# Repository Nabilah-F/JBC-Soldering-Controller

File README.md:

# JBC-Soldering-Controller

The idea of this project is to make a JBC soldering station for the T245, T210, HT420 and PA120 Micro Tweezers. 
It runs from a 12V to 24V DC power supply.

Tested:

T245 soldering iron

Todo:

Automatically changing the GUI depending on if you are using the standard iron or the tweezers.
Update FW to use tweezers.

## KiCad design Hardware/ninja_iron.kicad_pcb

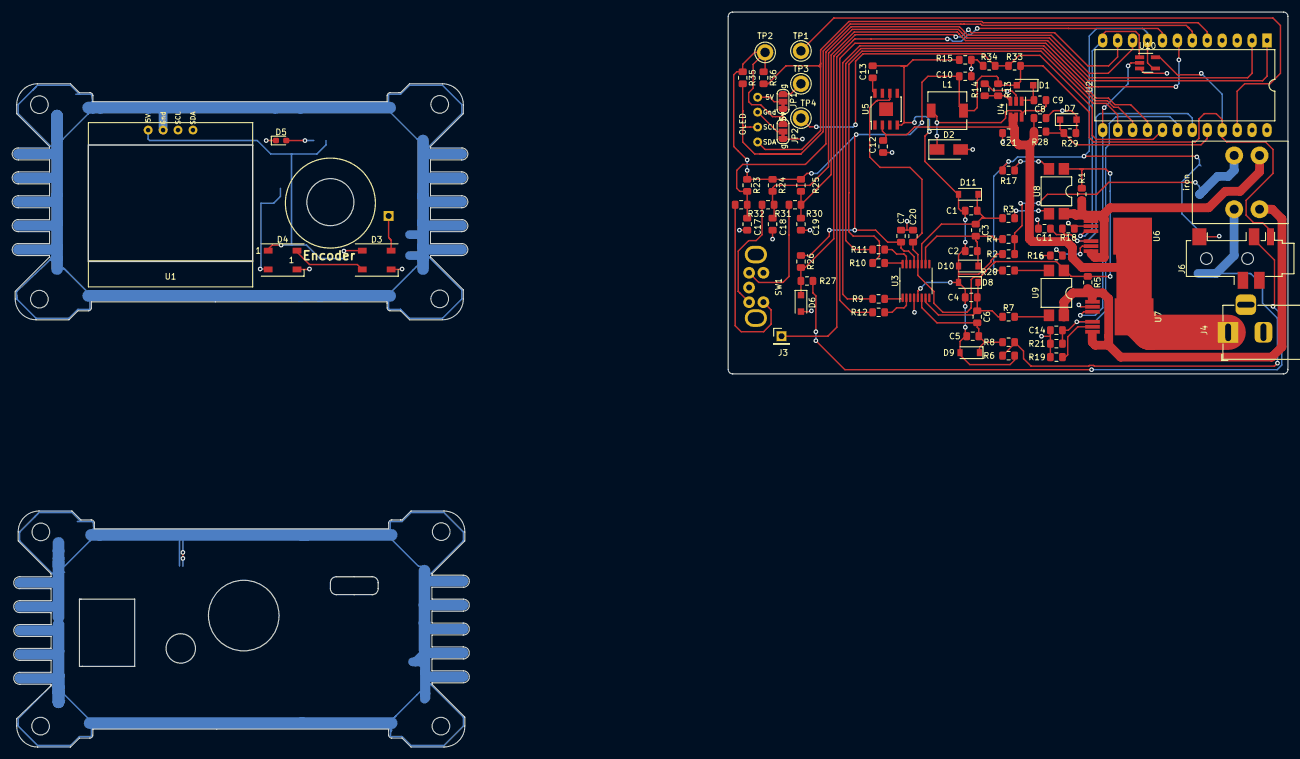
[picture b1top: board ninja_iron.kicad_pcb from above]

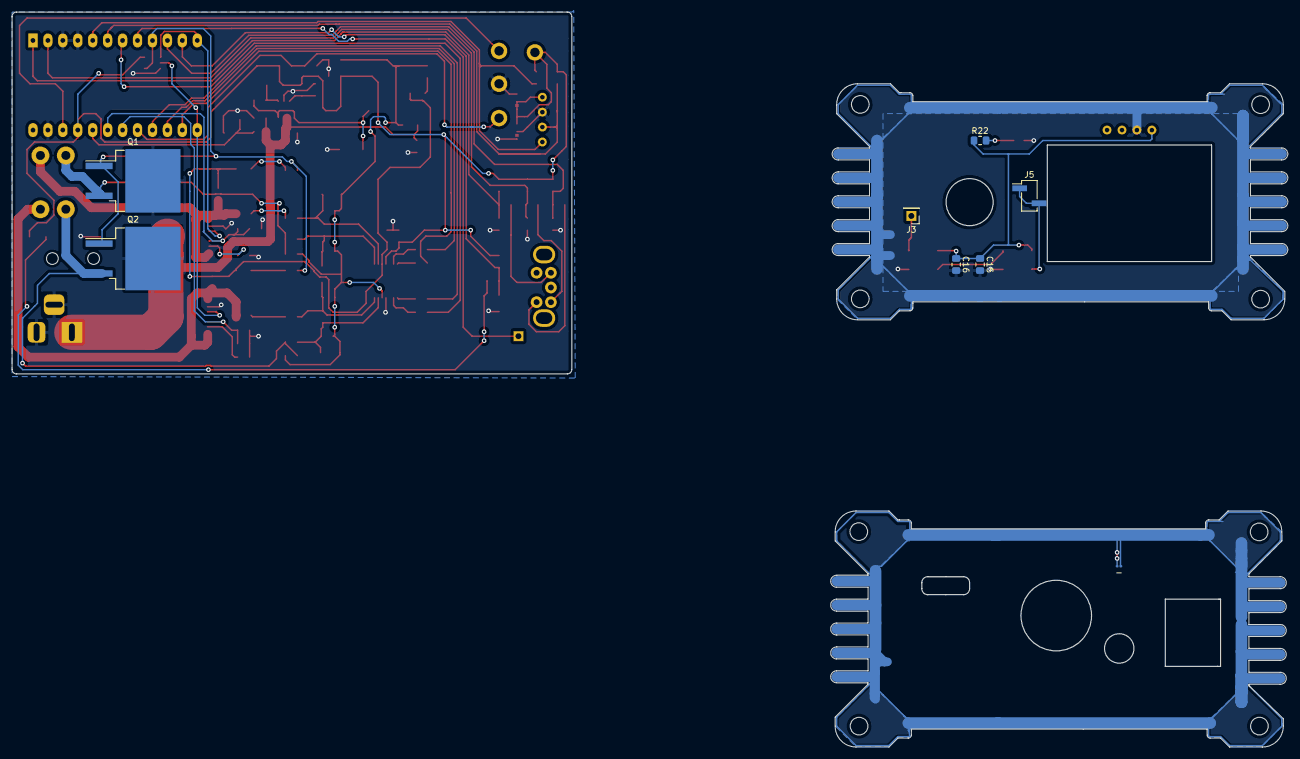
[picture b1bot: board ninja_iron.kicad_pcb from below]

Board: 2 copper layers, 216.8 x 124.9 mm, 96 parts (8 on the bottom side), 52 nets.

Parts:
-: R_0201_0603Metric
C1, C2, C4, C5: 0.047uF; C_0805_2012Metric_Pad1.15x1.40mm_HandSolder
C3, C6: 0.47uF; C_0805_2012Metric_Pad1.15x1.40mm_HandSolder
C7, C9, C12, C13, C15, C16, C20: 0.1uF; C_0805_2012Metric_Pad1.15x1.40mm_HandSolder
C8: 10uF; C_0805_2012Metric_Pad1.15x1.40mm_HandSolder
C10: 20uF; C_0805_2012Metric_Pad1.15x1.40mm_HandSolder
C11, C14, C17, C18, C19: 10nF; C_0805_2012Metric_Pad1.15x1.40mm_HandSolder
C21: 1uF; C_0805_2012Metric_Pad1.15x1.40mm_HandSolder
D1: 1N4448; D_SOD-123F
D2: B140-E3; D_SMA
D3, D4: WS2812B; LED_WS2812B_PLCC4_5.0x5.0mm_P3.2mm
D5: LED; LED_0603_1608Metric_Pad1.05x0.95mm_HandSolder
D6, D7: D; D_SOD-123F
D8, D9, D10, D11: 4V7; D_SOD-123
J3, J3#2: Conn_01x01; PinHeader_1x01_P2.54mm_Vertical
J4: Barrel_Jack_Switch; BarrelJack_Horizontal
J5: Conn_01x01; PinHeader_1x02_P2.54mm_Vertical_SMD_Pin1Left
J6: Audio-Jack-3; Jack_3.5mm_Horizontal
JP1, JP2: -; SolderJumper-3_P1.3mm_Bridged12_RoundedPad1.0x1.5mm_NumberL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
L1: 22uH; L_6.3x6.3_H3
OLED: pin_oled
Q1, Q2: Q_NMOS_GSD; TO-263-2
R1, R2, R5, R6: 100k; R_0805_2012Metric_Pad1.15x1.40mm_HandSolder
R3, R4, R7, R8: 820; R_0805_2012Metric_Pad1.15x1.40mm_HandSolder
R9, R10, R11, R12: 51; R_0805_2012Metric_Pad1.15x1.40mm_HandSolder
R13: 52.3k; R_0805_2012Metric_Pad1.15x1.40mm_HandSolder
R14, R16, R19, R23, R24, R25, R26, R35, R36: 10k; R_0805_2012Metric_Pad1.15x1.40mm_HandSolder
R15: 0R; R_0805_2012Metric_Pad1.15x1.40mm_HandSolder
R17, R20: 750R; R_0805_2012Metric_Pad1.15x1.40mm_HandSolder
R18, R21: 1k2; R_0805_2012Metric_Pad1.15x1.40mm_HandSolder
R22: 330; R_0805_2012Metric_Pad1.15x1.40mm_HandSolder
R27, R30, R31, R32: 100; R_0805_2012Metric_Pad1.15x1.40mm_HandSolder
R28: 30k; R_0805_2012Metric_Pad1.15x1.40mm_HandSolder
R29: 5k1; R_0805_2012Metric_Pad1.15x1.40mm_HandSolder
R33, R34: DNF; R_0805_2012Metric_Pad1.15x1.40mm_HandSolder
SW1: Rotary_Encoder_Switch; rot_encoder_alt
TP1, TP2, TP3, TP4: TestPoint; TestPoint_Keystone_5005-5009_Compact
U1: OLED_I2C_128x32; OLED_I2C_128x32_alt
U2: arduino_pro_micro; DIP-24_W15.24mm_LongPads
U3: ADS1120-PW; TSSOP-16_4.4x5mm_P0.65mm
U4: MCP16301; SOT-23-6_Handsoldering
U5: AD586; SOIC-8-1EP_3.9x4.9mm_P1.27mm_EP2.35x2.35mm
U6, U7: VN5E010; HPAK
U8, U9: FODM3011; SMDIP-4_W7.62mm
U10: 74LVC1G32; SOT-23-5_HandSoldering
iron: neutrik_modified

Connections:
+5VA: C20.1, R1.2, R5.1, U3.12, U5.6, U8.1, U9.1
+5VD: C7.1, C10.1, C15.1, C16.1, D1.2, D3.1, D4.1, J6.1, JP1.1, JP1.2, JP2.3, L1.2, OLED.1, R13.1, R22.1, R23.1, R24.1, R25.1, R26.1, R33.1, R35.1, R36.1, TP2.1, U1.1, U2.21, U3.13, U10.5
+24V: C8.1, C12.1, C21.1, J4.1, R28.1, U4.4, U4.5, U5.2, U6.4, U7.4
/Clk: R9.1, U2.16
/Current_sense_0: C11.1, R18.1, U2.19, U6.5
/Current_sense_1: C14.1, R21.1, U2.18, U7.5
/Heater0: R1.1, U6.1, U6.7, U8.4, iron.5
/Heater1: R5.2, U7.1, U7.7, U9.4, iron.3
/Heater_pwm_0: U2.12, U6.3, U10.1
/Heater_pwm_1: U2.13, U7.3, U10.2
/MISO: R11.1, U2.15
/MOSI: R10.1, U2.14
/VinDev: D7.1, R28.2, R29.1, U2.20
/\CS: R12.1, U2.7
/aIn: C19.1, R25.2, R30.1, U2.1
/bIn: C18.1, R24.2, R31.1, U2.2
/led_data: D3.4, J3.1, J3#2.1, U2.8
/low_mosfet_0: Q1.1, Q2.1, R17.2, R20.2, U2.9, U10.4
/sleepIn: D6.1, R26.2, R27.2, U2.11
/swIn: C17.1, R23.2, R32.2, U2.10
GND: -.1, -.2, C7.2, C8.2, C10.2, C11.2, C12.2, C14.2, C15.2, C16.2, C17.2, C18.2, C19.2, C20.2, C21.2, D2.2, D3.3, D4.3, D5.1, D6.2, D7.2, J4.2, J4.3, J6.3, JP1.3, JP2.1, JP2.2, OLED.2, Q1.2, Q2.2, R14.2, R15.1, R16.2, R18.2, R19.2, R21.2, R29.2, R34.2, TP3.1, U1.2, U2.3, U2.4, U2.23, U3.4, U4.2, U6.2, U7.2, U10.3
GNDA: C1.1, C2.2, C4.1, C5.2, C13.2, D8.2, D9.2, D10.2, D11.2, R2.1, R6.2, R15.2, U3.5, U5.4
unnamed: C1.2, C3.1, D11.1, R3.1, U3.11
unnamed: C2.1, C3.2, D10.1, R4.1, U3.10
unnamed: C4.2, C6.1, D8.1, R7.1, U3.7
unnamed: C5.1, C6.2, D9.1, R8.1, U3.6
unnamed: C9.1, D1.1, U4.1
unnamed: C9.2, D2.1, L1.1, U4.6
unnamed: C13.1, U5.8
unnamed: D3.2, D4.4
unnamed: D4.2, J5.1, J5.2
unnamed: D5.2, R22.2
unnamed: Q1.3, R2.2, R4.2, iron.4
unnamed: Q2.3, R6.1, R8.2, iron.2
unnamed: J6.2, R27.1
unnamed: R3.2, U8.3
unnamed: R7.2, U9.3
unnamed: R9.2, U3.1
unnamed: R10.2, U3.16
unnamed: R11.2, U3.15
unnamed: R12.2, U3.2
unnamed: R13.2, R14.1, U4.3
unnamed: R16.1, U6.6
unnamed: R17.1, U8.2
unnamed: R19.1, U7.6
unnamed: R20.1, U9.2
unnamed: R33.2, R34.1, TP4.1, U2.17
unnamed: U1.3, U2.6
unnamed: U1.4, U2.5
unnamed: TP1.1, U2.22
unnamed: OLED.3, R35.2
unnamed: OLED.4, R36.2

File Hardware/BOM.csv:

Reference, Quantity, Value, Footprint, Datasheet
C1 C2 C4 C5 ,4,"0.047uF","Capacitor_SMD:C_0805_2012Metric_Pad1.15x1.40mm_HandSolder","~"
C10 ,1,"20uF","Capacitor_SMD:C_0805_2012Metric_Pad1.15x1.40mm_HandSolder","~"
C11 C14 C17 C18 C19 ,5,"10nF","Capacitor_SMD:C_0805_2012Metric_Pad1.15x1.40mm_HandSolder","~"
C21 ,1,"1uF","Capacitor_SMD:C_0805_2012Metric_Pad1.15x1.40mm_HandSolder","~"
C3 C6 ,2,"0.47uF","Capacitor_SMD:C_0805_2012Metric_Pad1.15x1.40mm_HandSolder","~"
C7 C20 C9 C12 C13 C15 C16 ,7,"0.1uF","Capacitor_SMD:C_0805_2012Metric_Pad1.15x1.40mm_HandSolder","~"
C8 ,1,"10uF","Capacitor_SMD:C_0805_2012Metric_Pad1.15x1.40mm_HandSolder","~"
D1 ,1,"1N4448","Diode_SMD:D_SOD-123F","http://www.nxp.com/documents/data_sheet/1N4148_1N4448.pdf"
D10 D11 D8 D9 ,4,"4V7","Diode_SMD:D_SOD-123","~"
D2 ,1,"B140-E3","Diode_SMD:D_SMA","http://www.vishay.com/docs/88946/b120.pdf"
D3 D4 ,2,"WS2812B","LED_SMD:LED_WS2812B_PLCC4_5.0x5.0mm_P3.2mm","https://cdn-shop.adafruit.com/datasheets/WS2812B.pdf"
D5 ,1,"LED","LED_SMD:LED_0603_1608Metric_Pad1.05x0.95mm_HandSolder","~"
D6 D7 ,2,"D","Diode_SMD:D_SOD-123F","~"
J1 J2 ,2,"JBC_iron","Connector_Phoenix_MSTB:PhoenixContact_MSTBVA_2,5_3-G-5,08_1x03_P5.08mm_Vertical",""
J3 J7 ,2,"Conn_01x01","Connector_PinHeader_2.54mm:PinHeader_1x01_P2.54mm_Vertical","~"
J4 ,1,"Barrel_Jack_Switch","Connector_BarrelJack:BarrelJack_Horizontal","~"
J6 ,1,"Audio-Jack-3","footprints:Jack_3.5mm_Horizontal",""
L1 ,1,"22uH","Inductor_SMD:L_6.3x6.3_H3",""
Q1 Q2 ,2,"Q_NMOS_GSD","Package_TO_SOT_SMD:TO-263-2","~"
R1 R2 R5 R6 ,4,"100k","Resistor_SMD:R_0805_2012Metric_Pad1.15x1.40mm_HandSolder","~"
R13 ,1,"52.3k","Resistor_SMD:R_0805_2012Metric_Pad1.15x1.40mm_HandSolder","~"
R14 R16 R19 R23 R24 R25 R26 R35 R36 ,9,"10k","Resistor_SMD:R_0805_2012Metric_Pad1.15x1.40mm_HandSolder","~"
R15 ,1,"0R","Resistor_SMD:R_0805_2012Metric_Pad1.15x1.40mm_HandSolder","~"
R17 R20 ,2,"750R","Resistor_SMD:R_0805_2012Metric_Pad1.15x1.40mm_HandSolder","~"
R18 R21 ,2,"1k2","Resistor_SMD:R_0805_2012Metric_Pad1.15x1.40mm_HandSolder","~"
R22 ,1,"330","Resistor_SMD:R_0805_2012Metric_Pad1.15x1.40mm_HandSolder","~"
R27 R30 R31 R32 ,4,"100","Resistor_SMD:R_0805_2012Metric_Pad1.15x1.40mm_HandSolder","~"
R28 ,1,"30k","Resistor_SMD:R_0805_2012Metric_Pad1.15x1.40mm_HandSolder","~"
R29 ,1,"5k1","Resistor_SMD:R_0805_2012Metric_Pad1.15x1.40mm_HandSolder","~"
R3 R4 R7 R8 ,4,"820","Resistor_SMD:R_0805_2012Metric_Pad1.15x1.40mm_HandSolder","~"
R33 R34 ,2,"DNF","Resistor_SMD:R_0805_2012Metric_Pad1.15x1.40mm_HandSolder","~"
R9 R10 R11 R12 ,4,"51","Resistor_SMD:R_0805_2012Metric_Pad1.15x1.40mm_HandSolder","~"
SW1 ,1,"Rotary_Encoder_Switch","footprints:rot_encoder_alt","~"
TP1 TP2 TP3 TP4 ,4,"TestPoint","TestPoint:TestPoint_Keystone_5005-5009_Compact","~"
U1 ,1,"OLED_I2C_128x32","footprints:OLED_I2C_128x32_alt",""
U10 ,1,"74LVC1G32","Package_TO_SOT_SMD:SOT-23-5_HandSoldering","http://www.ti.com/lit/sg/scyt129e/scyt129e.pdf"
U2 ,1,"arduino_pro_micro","Package_DIP:DIP-24_W15.24mm_LongPads",""
U3 ,1,"ADS1120-PW","Package_SO:TSSOP-16_4.4x5mm_P0.65mm","http://www.ti.com/lit/ds/symlink/ads1120.pdf"
U4 ,1,"MCP16301","Package_TO_SOT_SMD:SOT-23-6_Handsoldering",""
U5 ,1,"AD586","Package_SO:SOIC-8-1EP_3.9x4.9mm_P1.27mm_EP2.35x2.35mm","http://www.analog.com/media/en/technical-documentation/data-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"
U6 U7 ,2,"VN5E010","footprints:HPAK",""
U8 U9 ,2,"FODM3011","Package_DIP:SMDIP-4_W7.62mm","http://www.fairchildsemi.com/ds/FO/FODM3053.pdf"

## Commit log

2021-01-23 updated ADC to work with a wider range of thermocouples
